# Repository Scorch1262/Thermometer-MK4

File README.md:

Datenblatt

Status:				Fertig
Bezeichnung:			Thermometer MK4
Auftragsnummer:			
Auftraggeber:			Privat
Designer:			Torben Bott
Beschreibung:			Luftdruck und Themperatur Sensor mit OLED Anzeige, Lipo Akku und UART Schnittstelle 
			
Letzte Änderung:		23.04.2020

Versorgungsspannung (Normal):	5V
Versorgungsspannung (Min.):	5V
Versorgungsspannung (Max.):	5V
Interne Spannungen:		5V / 3,7V
		
Frequenz: 			16MHz
Prozessor: 			PIC18F46K20

Sensor:
https://github.com/jrmcguire/BME280

Display:
https://pic-projekte.de/blog/ssd1306/
https://github.com/PIC-Nico/SSD1306
https://pic-projekte.de/forum/viewtopic.php?f=3&t=104

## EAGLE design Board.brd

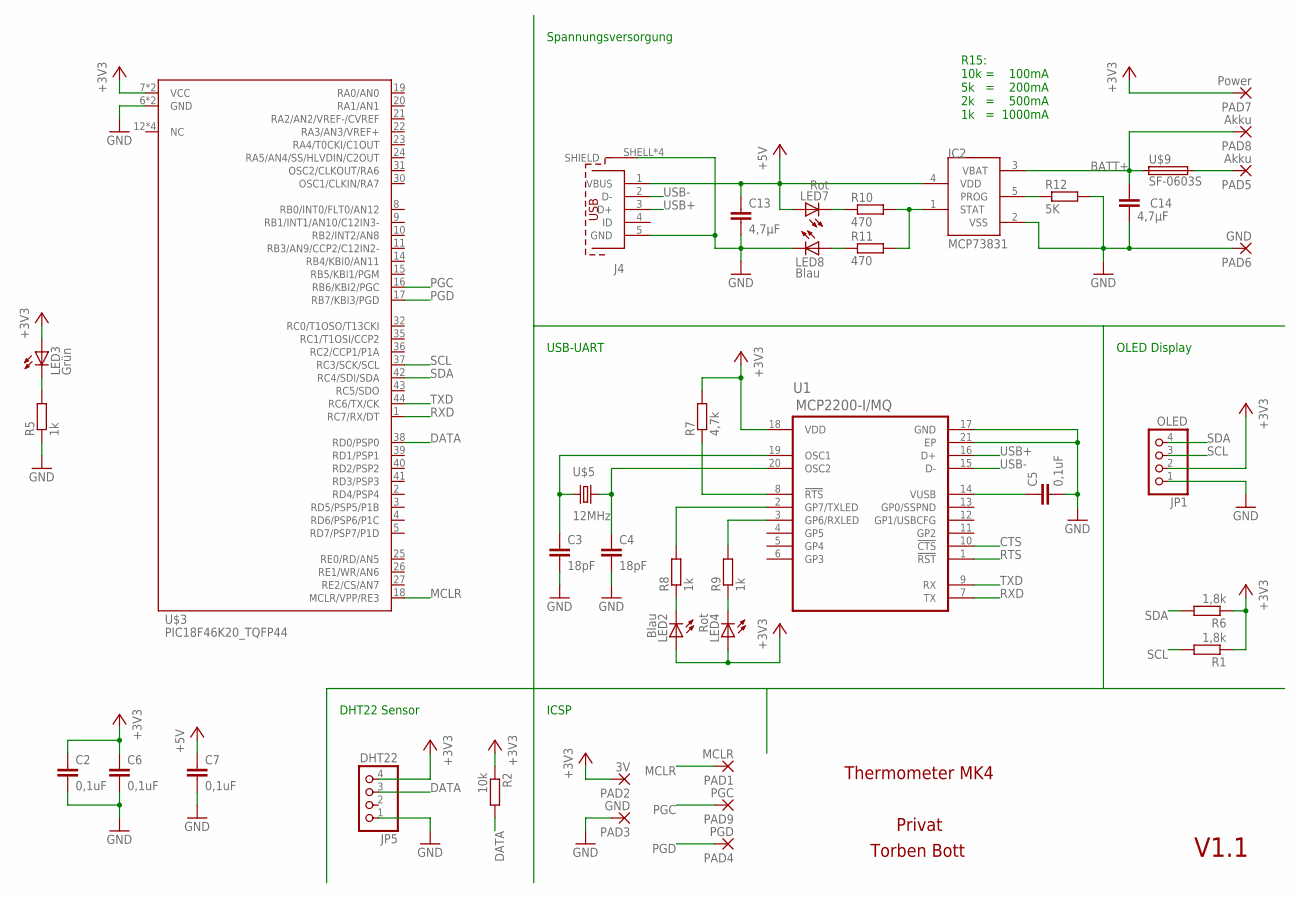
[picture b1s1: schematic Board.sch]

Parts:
C2, C5, C6, C7: 0,1uF; C0805
C3, C4: 18pF; C0805
C13, C14: 4,7µF; C0805
IC2: MCP73831; SOT23-5L
J4: 629105136821
JP1: OLED; 1X04
JP5: DHT22; 1X04
LED2, LED8: Blau; CHIPLED_0805
LED3: Grün; CHIPLED_0805
LED4, LED7: Rot; CHIPLED_0805
PAD1: MCLR; SMD1,27-2,54
PAD2: 3V; SMD1,27-2,54
PAD3: GND; SMD1,27-2,54
PAD4: PGD; SMD1,27-2,54
PAD5, PAD8: Akku; 5-1,8
PAD6: GND; 5-1,8
PAD7: Power; 5-1,8
PAD9: PGC; SMD1,27-2,54
R1, R6: 1,8k; R0805
R2: 10k; R0805
R5, R8, R9: 1k; R0805
R7: 4,7k; R0805
R10, R11: 470; R0805
R12: 5K; R0805
U1: MCP2200-I/MQ; QFN65P500X500X100-21N
U$3: PIC18F46K20_TQFP44; TQFP44
U$5: 12MHz; 7M_SERIES
U$9: SF-0603S; R0603

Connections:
+3V3: C2.1, C6.1, JP1.2, JP5.4, LED2.A, LED3.A, LED4.A, PAD2.1, PAD7.1, R1.1, R2.1, R6.1, R7.2, U1.18 (VDD), U$3.7 (VCC), U$3.28 (VCC)
+5V: C7.1, C13.1, IC2.4 (VDD), J4.1 (VBUS), LED7.A
BATT+: C14.1, IC2.3 (VBAT), PAD8.1, U$9.1
CTS: U1.10 (!CTS)
DATA: JP5.3, R2.2, U$3.38 (RD0/PSP0)
GND: C2.2, C3.2, C4.2, C5.2, C6.2, C7.2, C13.2, C14.2, IC2.2 (VSS), J4.5 (GND), J4.SHELL (SHIELD), J4.SHELL1 (SHIELD), J4.SHELL2 (SHIELD), J4.SHELL3 (SHIELD), JP1.1, JP5.1, LED8.C, PAD3.1, PAD6.1, R5.1, R12.2, U1.17 (GND), U1.21 (EP), U$3.6 (GND), U$3.29 (GND)
MCLR: PAD1.1, U$3.18 (MCLR/VPP/RE3)
unnamed: C4.1, U1.20 (OSC2), U$5.3 (2)
unnamed: LED3.C, R5.2
unnamed: C3.1, U1.19 (OSC1), U$5.1
unnamed: R7.1, U1.8 (!RTS)
unnamed: R8.2, U1.2 (GP7/TXLED)
unnamed: R9.2, U1.3 (GP6/RXLED)
unnamed: C5.1, U1.14 (VUSB)
unnamed: LED2.C, R8.1
unnamed: LED4.C, R9.1
unnamed: IC2.1 (STAT), R10.2, R11.2
unnamed: LED7.C, R10.1
unnamed: LED8.A, R11.1
unnamed: IC2.5 (PROG), R12.1
unnamed: PAD5.1, U$9.2
PGC: PAD9.1, U$3.16 (RB6/KBI2/PGC)
PGD: PAD4.1, U$3.17 (RB7/KBI3/PGD)
RTS: U1.1 (!RST)
RXD: U1.7 (TX), U$3.1 (RC7/RX/DT)
SCL: JP1.3, R1.2, U$3.37 (RC3/SCK/SCL)
SDA: JP1.4, R6.2, U$3.42 (RC4/SDI/SDA)
TXD: U1.9 (RX), U$3.44 (RC6/TX/CK)
USB+: J4.3 (D+), U1.16 (D+)
USB-: J4.2 (D-), U1.15 (D-)

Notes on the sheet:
Torben Bott
ICSP
OLED Display
Privat
V1.1
Thermometer MK4
Spannungsversorgung
R15: 10k = 100mA 5k = 200mA 2k = 500mA 1k = 1000mA
USB-UART
DHT22 Sensor

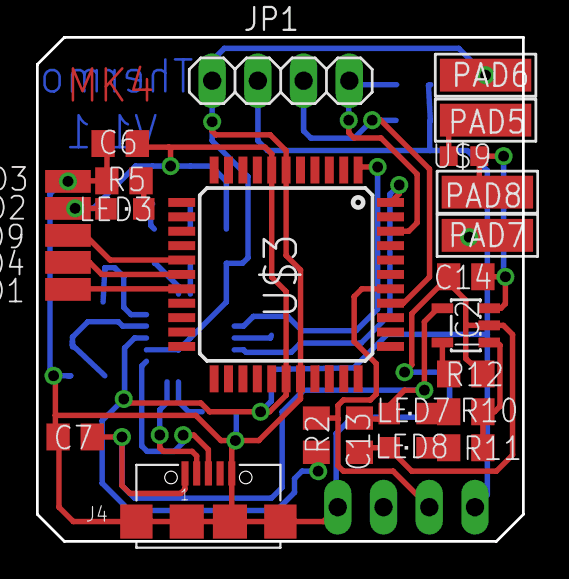
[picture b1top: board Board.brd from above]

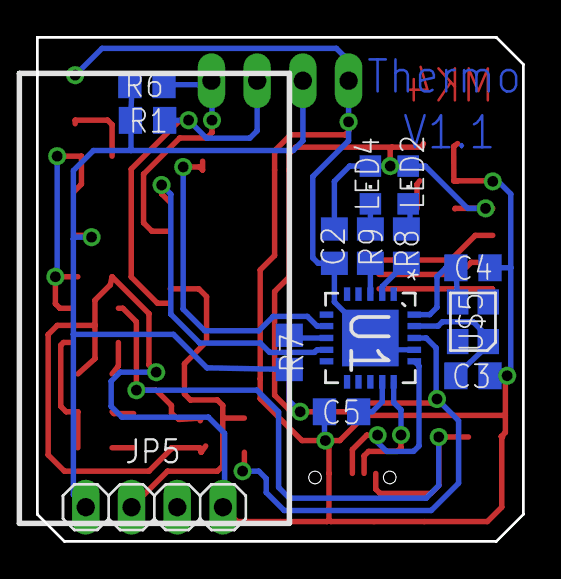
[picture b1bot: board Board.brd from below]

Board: 2 copper layers, 27.0 x 28.0 mm, 40 parts (14 on the bottom side), 28 nets.

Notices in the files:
parts and their libraries:
InputOutputIO: Copyright: Würth Elektronik
